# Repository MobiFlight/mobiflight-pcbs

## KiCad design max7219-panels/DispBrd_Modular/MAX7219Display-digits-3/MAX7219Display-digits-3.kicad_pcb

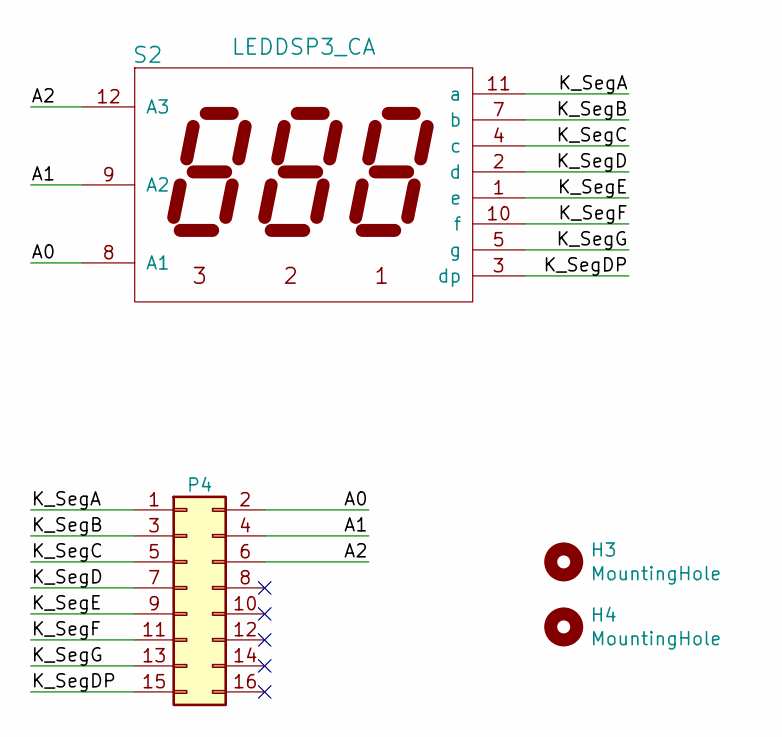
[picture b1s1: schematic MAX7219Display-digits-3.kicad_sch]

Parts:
H3, H4: MountingHole; Hole3mm
P4: Conn_02x08_Odd_Even; IDC-Header_2x08_P2.54mm_Vertical
S2: LEDDSP3_CA; Disp7s3x_036

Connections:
/A0: P4.2, S2.8 (A1)
/A1: P4.4, S2.9 (A2)
/A2: P4.6, S2.12 (A3)
/K_SegA: P4.1, S2.11 (a)
/K_SegB: P4.3, S2.7 (b)
/K_SegC: P4.5, S2.4 (c)
/K_SegD: P4.7, S2.2 (d)
/K_SegDP: P4.15, S2.3 (dp)
/K_SegE: P4.9, S2.1 (e)
/K_SegF: P4.11, S2.10 (f)
/K_SegG: P4.13, S2.5 (g)

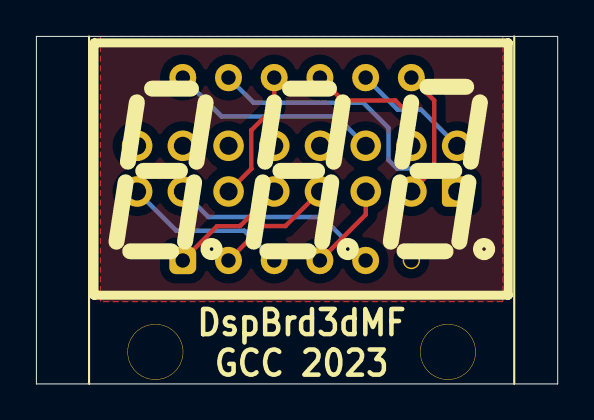
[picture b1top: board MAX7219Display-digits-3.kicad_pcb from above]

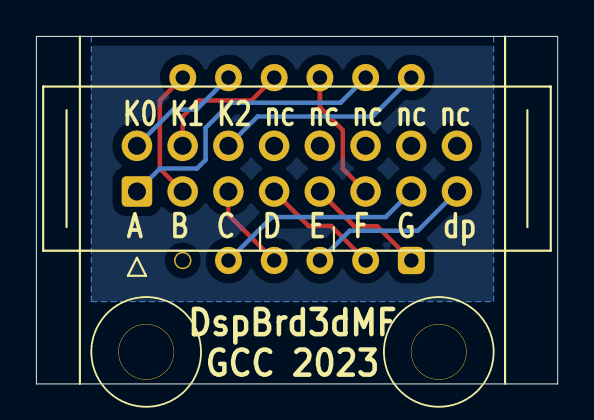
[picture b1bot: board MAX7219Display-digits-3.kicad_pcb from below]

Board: 2 copper layers, 29.0 x 19.3 mm, 4 parts (3 on the bottom side), 11 nets.

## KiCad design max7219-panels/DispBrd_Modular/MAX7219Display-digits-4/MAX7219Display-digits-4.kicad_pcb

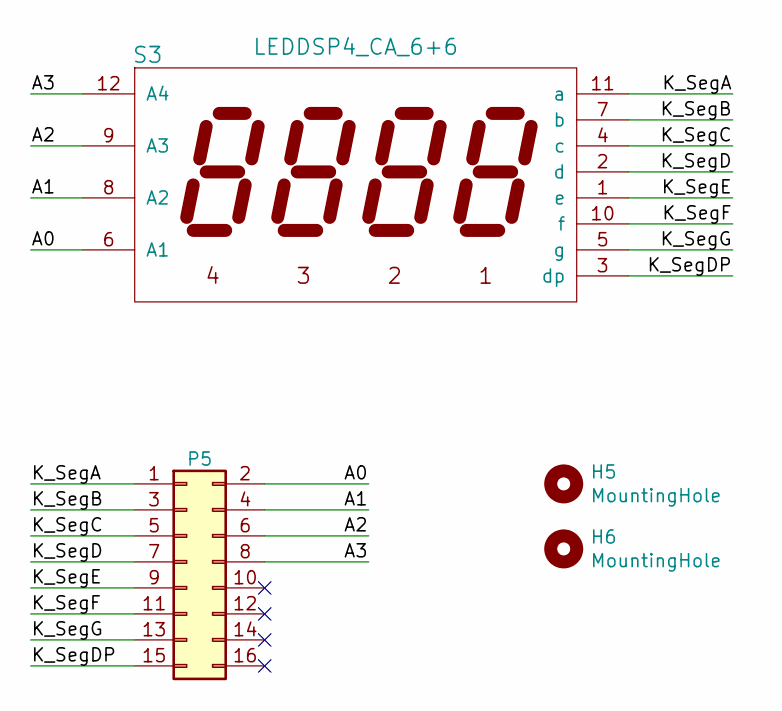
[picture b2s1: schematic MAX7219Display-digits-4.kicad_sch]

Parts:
H5, H6: MountingHole; Hole3mm
P5: Conn_02x08_Odd_Even; IDC-Header_2x08_P2.54mm_Vertical
S3: LEDDSP4_CA_6+6; Disp7s4x_036_6+6

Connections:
/A0: P5.2, S3.6 (A1)
/A1: P5.4, S3.8 (A2)
/A2: P5.6, S3.9 (A3)
/A3: P5.8, S3.12 (A4)
/K_SegA: P5.1, S3.11 (a)
/K_SegB: P5.3, S3.7 (b)
/K_SegC: P5.5, S3.4 (c)
/K_SegD: P5.7, S3.2 (d)
/K_SegDP: P5.15, S3.3 (dp)
/K_SegE: P5.9, S3.1 (e)
/K_SegF: P5.11, S3.10 (f)
/K_SegG: P5.13, S3.5 (g)

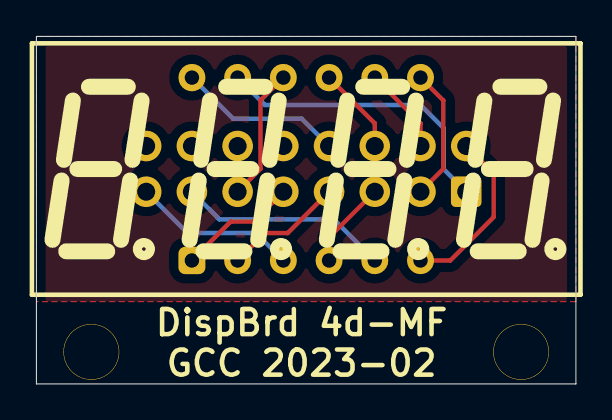
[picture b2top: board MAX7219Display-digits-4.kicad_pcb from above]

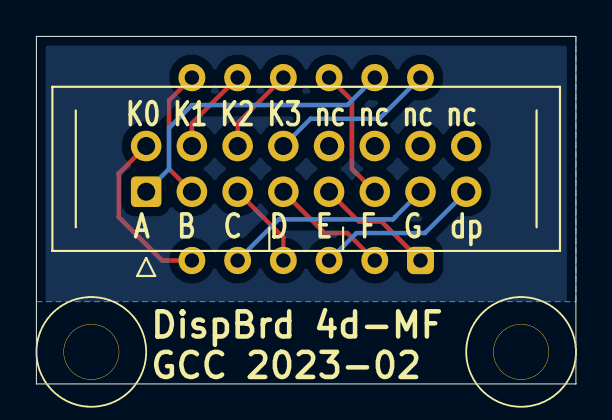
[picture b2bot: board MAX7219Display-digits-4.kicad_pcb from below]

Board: 2 copper layers, 30.0 x 19.3 mm, 4 parts (3 on the bottom side), 12 nets.

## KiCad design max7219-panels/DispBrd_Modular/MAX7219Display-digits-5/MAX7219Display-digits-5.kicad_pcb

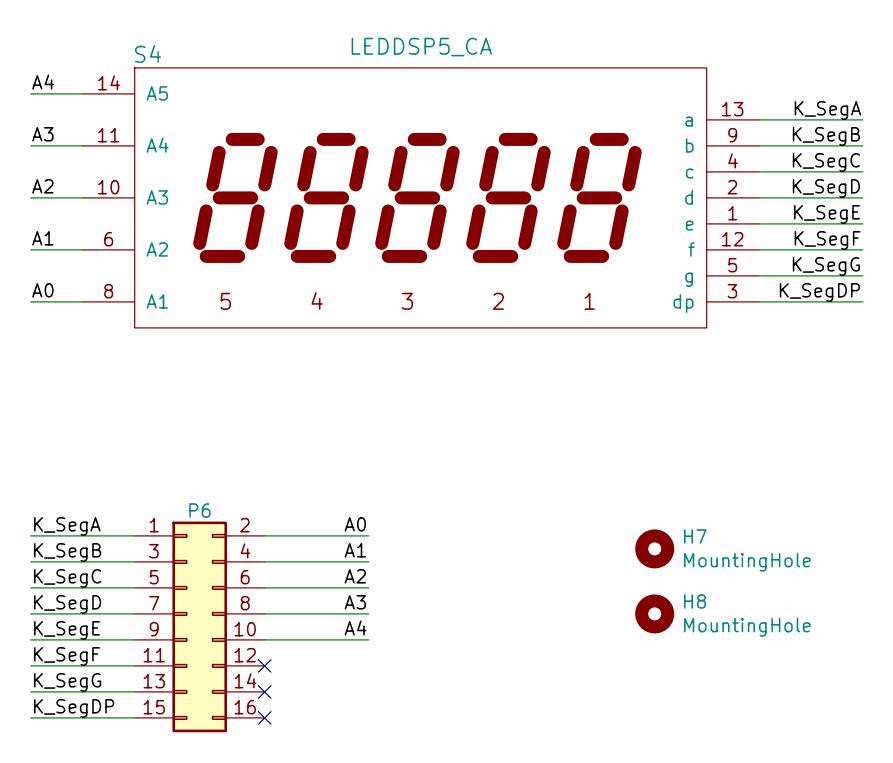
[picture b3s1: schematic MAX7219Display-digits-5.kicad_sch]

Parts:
H7, H8: MountingHole; Hole3mm
P6: Conn_02x08_Odd_Even; IDC-Header_2x08_P2.54mm_Vertical
S4: LEDDSP5_CA; Disp7s5x_036

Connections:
/A0: P6.2, S4.8 (A1)
/A1: P6.4, S4.6 (A2)
/A2: P6.6, S4.10 (A3)
/A3: P6.8, S4.11 (A4)
/A4: P6.10, S4.14 (A5)
/K_SegA: P6.1, S4.13 (a)
/K_SegB: P6.3, S4.9 (b)
/K_SegC: P6.5, S4.4 (c)
/K_SegD: P6.7, S4.2 (d)
/K_SegDP: P6.15, S4.3 (dp)
/K_SegE: P6.9, S4.1 (e)
/K_SegF: P6.11, S4.12 (f)
/K_SegG: P6.13, S4.5 (g)

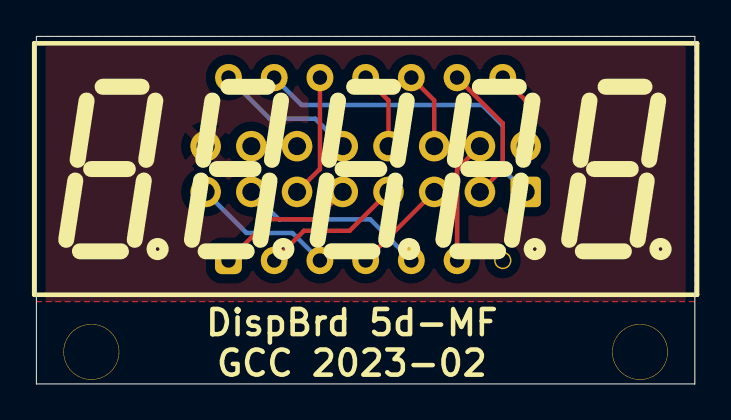
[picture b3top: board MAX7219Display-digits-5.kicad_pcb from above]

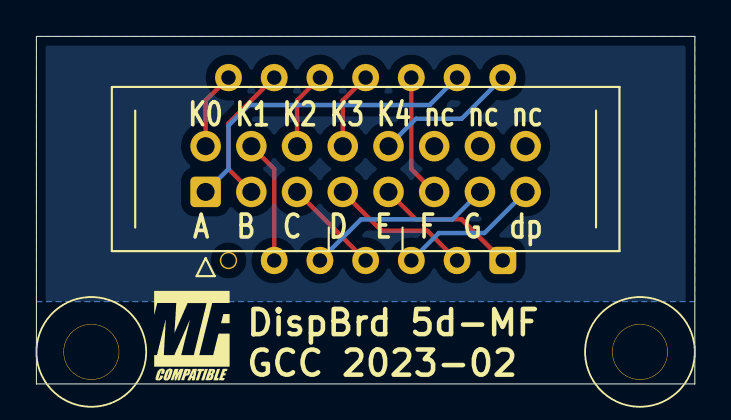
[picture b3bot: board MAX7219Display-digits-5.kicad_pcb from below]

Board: 2 copper layers, 36.6 x 19.3 mm, 4 parts (3 on the bottom side), 13 nets.

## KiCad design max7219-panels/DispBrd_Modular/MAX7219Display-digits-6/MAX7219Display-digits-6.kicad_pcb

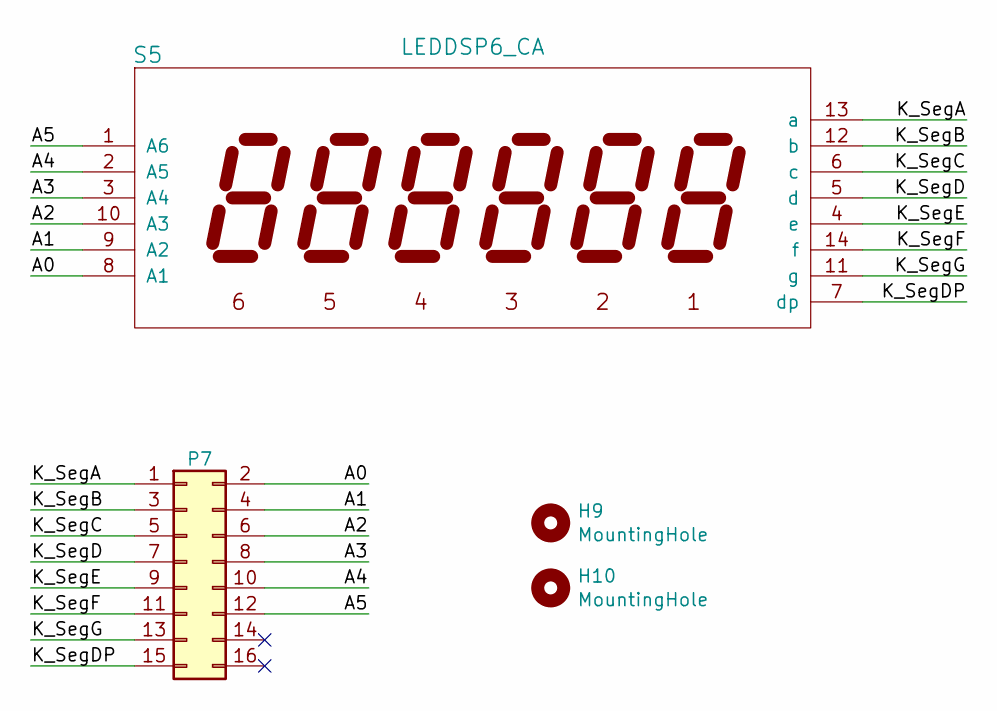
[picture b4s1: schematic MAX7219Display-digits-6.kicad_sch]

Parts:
H9, H10: MountingHole; Hole3mm
P7: Conn_02x08_Odd_Even; IDC-Header_2x08_P2.54mm_Vertical
S5: LEDDSP6_CA; Disp7s6x_036

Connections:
/A0: P7.2, S5.8 (A1)
/A1: P7.4, S5.9 (A2)
/A2: P7.6, S5.10 (A3)
/A3: P7.8, S5.3 (A4)
/A4: P7.10, S5.2 (A5)
/A5: P7.12, S5.1 (A6)
/K_SegA: P7.1, S5.13 (a)
/K_SegB: P7.3, S5.12 (b)
/K_SegC: P7.5, S5.6 (c)
/K_SegD: P7.7, S5.5 (d)
/K_SegDP: P7.15, S5.7 (dp)
/K_SegE: P7.9, S5.4 (e)
/K_SegF: P7.11, S5.14 (f)
/K_SegG: P7.13, S5.11 (g)

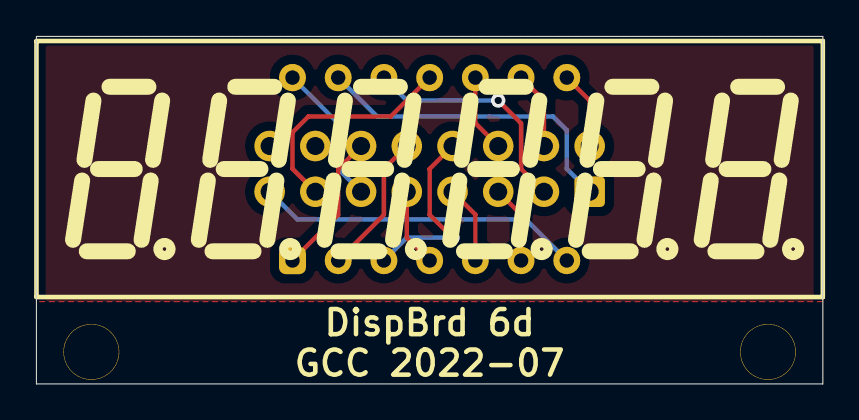
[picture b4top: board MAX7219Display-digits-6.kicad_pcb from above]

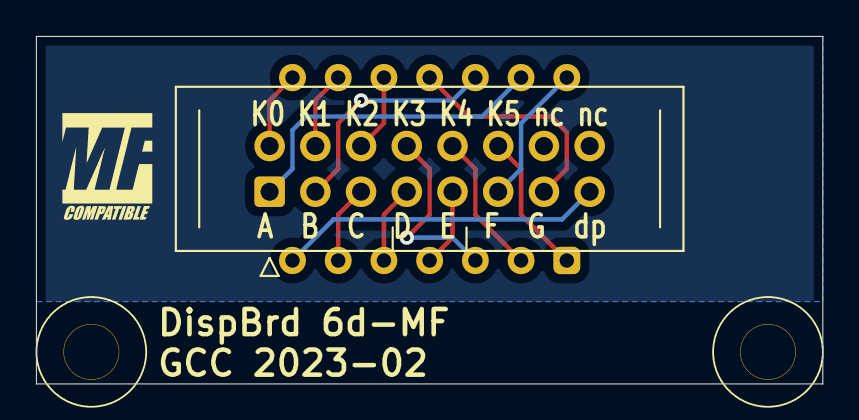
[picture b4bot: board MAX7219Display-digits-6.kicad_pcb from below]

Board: 2 copper layers, 43.7 x 19.3 mm, 4 parts (3 on the bottom side), 14 nets.

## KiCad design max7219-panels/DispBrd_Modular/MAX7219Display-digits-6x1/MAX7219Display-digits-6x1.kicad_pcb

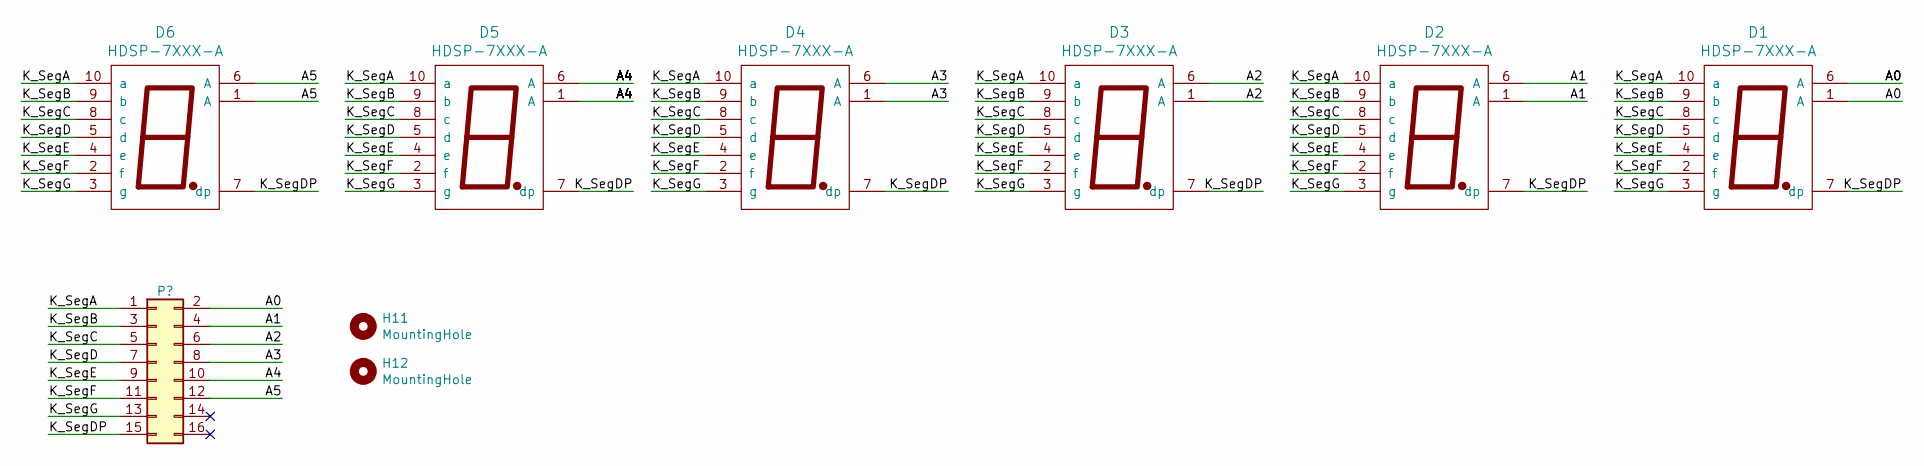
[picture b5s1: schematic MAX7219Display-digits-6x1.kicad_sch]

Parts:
D1, D2, D3, D4, D5, D6: HDSP-7XXX-A; Disp7_036
H11, H12: MountingHole; Hole3mm

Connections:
/A0: D1.1 (A), D1.6 (A); also elsewhere on the board
/A1: D2.1 (A), D2.6 (A); also elsewhere on the board
/A2: D3.1 (A), D3.6 (A); also elsewhere on the board
/A3: D4.1 (A), D4.6 (A); also elsewhere on the board
/A4: D5.1 (A), D5.6 (A); also elsewhere on the board
/A5: D6.1 (A), D6.6 (A); also elsewhere on the board
/K_SegA: D1.10 (a), D2.10 (a), D3.10 (a), D4.10 (a), D5.10 (a), D6.10 (a); also elsewhere on the board
/K_SegB: D1.9 (b), D2.9 (b), D3.9 (b), D4.9 (b), D5.9 (b), D6.9 (b); also elsewhere on the board
/K_SegC: D1.8 (c), D2.8 (c), D3.8 (c), D4.8 (c), D5.8 (c), D6.8 (c); also elsewhere on the board
/K_SegD: D1.5 (d), D2.5 (d), D3.5 (d), D4.5 (d), D5.5 (d), D6.5 (d); also elsewhere on the board
/K_SegDP: D1.7 (dp), D2.7 (dp), D3.7 (dp), D4.7 (dp), D5.7 (dp), D6.7 (dp); also elsewhere on the board
/K_SegE: D1.4 (e), D2.4 (e), D3.4 (e), D4.4 (e), D5.4 (e), D6.4 (e); also elsewhere on the board
/K_SegF: D1.2 (f), D2.2 (f), D3.2 (f), D4.2 (f), D5.2 (f), D6.2 (f); also elsewhere on the board
/K_SegG: D1.3 (g), D2.3 (g), D3.3 (g), D4.3 (g), D5.3 (g), D6.3 (g); also elsewhere on the board

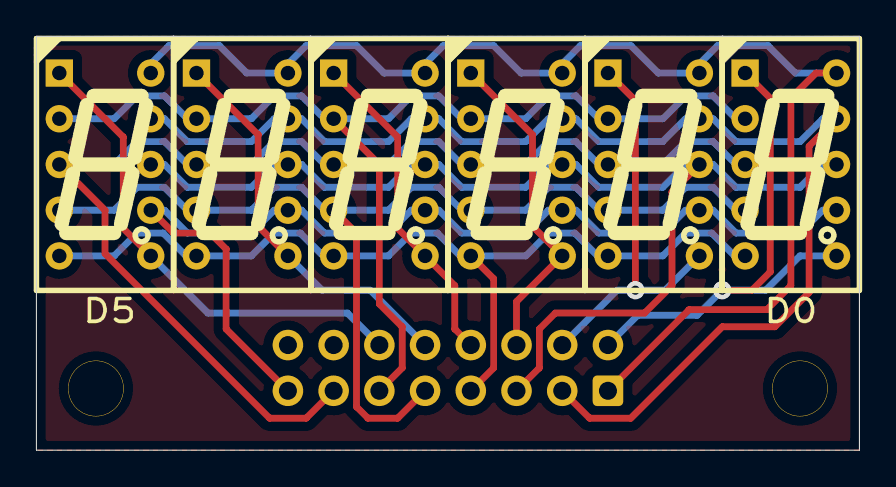
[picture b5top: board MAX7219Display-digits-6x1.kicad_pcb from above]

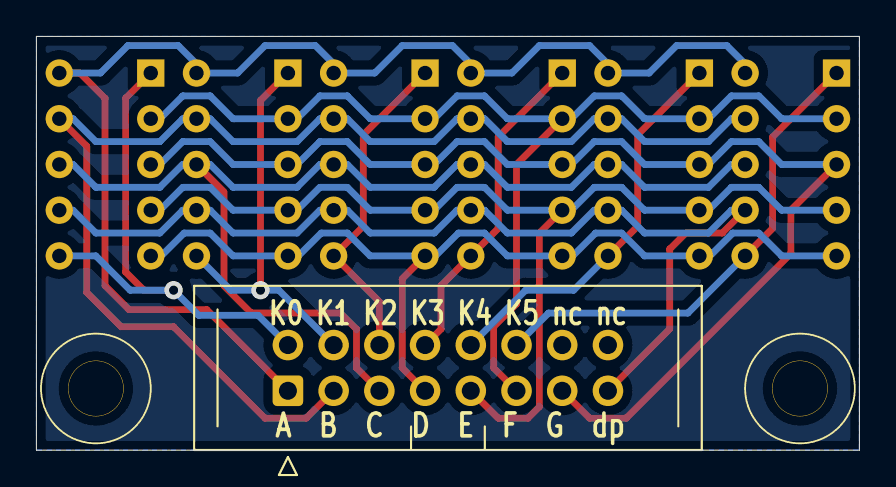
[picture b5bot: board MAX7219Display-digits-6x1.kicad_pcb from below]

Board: 2 copper layers, 45.7 x 23.0 mm, 9 parts (3 on the bottom side), 14 nets.

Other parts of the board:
P8: Conn_02x08_Odd_Even; IDC-Header_2x08_P2.54mm_Vertical

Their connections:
/A0: P8.2; also elsewhere on the board
/A1: P8.4; also elsewhere on the board
/A2: P8.6; also elsewhere on the board
/A3: P8.8; also elsewhere on the board
/A4: P8.10; also elsewhere on the board
/A5: P8.12; also elsewhere on the board
/K_SegA: P8.1; also elsewhere on the board
/K_SegB: P8.3; also elsewhere on the board
/K_SegC: P8.5; also elsewhere on the board
/K_SegD: P8.7; also elsewhere on the board
/K_SegDP: P8.15; also elsewhere on the board
/K_SegE: P8.9; also elsewhere on the board
/K_SegF: P8.11; also elsewhere on the board
/K_SegG: P8.13; also elsewhere on the board

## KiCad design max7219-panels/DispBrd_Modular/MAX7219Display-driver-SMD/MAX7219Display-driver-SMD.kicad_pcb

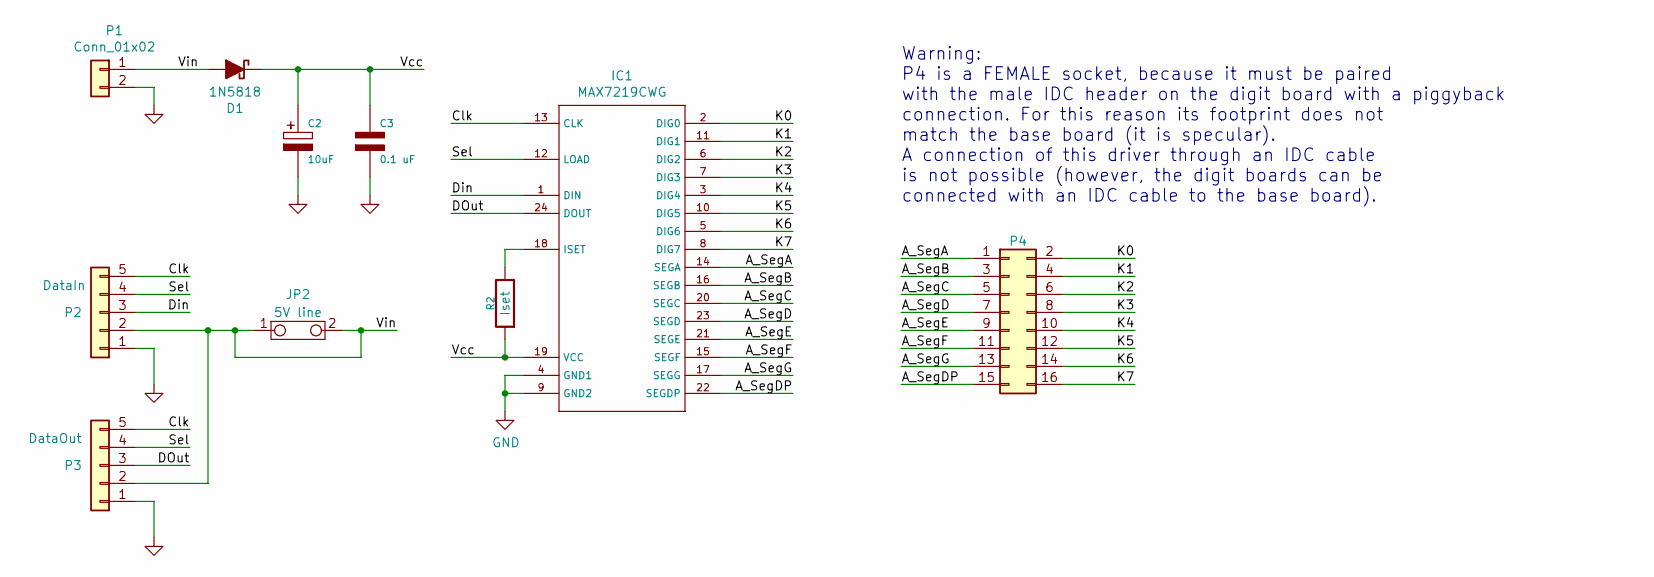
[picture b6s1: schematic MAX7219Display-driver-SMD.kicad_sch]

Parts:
C2: 10uF; CP_Radial_D5.0mm_P2.50mm
C3: 0.1 uF; C_1206_3216Metric_Pad1.42x1.75mm_HandSolder
D1: 1N5818; D_SMA_Handsoldering
IC1: MAX7219CWG; SOIC-24W_7.5x15.4mm_P1.27mm
JP2: 5V line; SolderJumper-2_P1.3mm_Bridged_Pad1.0x1.5mm
P1: Conn_01x02; PinHeader_1x02_P2.54mm_Vertical
P2: DataIn; JST_XH_B5B-XH-A_1x05_P2.50mm_Vertical
P3: DataOut; JST_XH_B5B-XH-A_1x05_P2.50mm_Vertical
P4: Conn_02x08_Odd_Even; PinSocket_2x08_P2.54mm_Vertical_SMD
R2: Iset; R_Axial_DIN0207_L6.3mm_D2.5mm_P10.16mm_Horizontal

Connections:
/A_SegA: IC1.14 (SEGA), P4.1
/A_SegB: IC1.16 (SEGB), P4.3
/A_SegC: IC1.20 (SEGC), P4.5
/A_SegD: IC1.23 (SEGD), P4.7
/A_SegDP: IC1.22 (SEGDP), P4.15
/A_SegE: IC1.21 (SEGE), P4.9
/A_SegF: IC1.15 (SEGF), P4.11
/A_SegG: IC1.17 (SEGG), P4.13
/Clk: IC1.13 (CLK), P2.5, P3.5
/DOut: IC1.24 (DOUT), P3.3
/Din: IC1.1 (DIN), P2.3
/K0: IC1.2 (DIG0), P4.2
/K1: IC1.11 (DIG1), P4.4
/K2: IC1.6 (DIG2), P4.6
/K3: IC1.7 (DIG3), P4.8
/K4: IC1.3 (DIG4), P4.10
/K5: IC1.10 (DIG5), P4.12
/K6: IC1.5 (DIG6), P4.14
/K7: IC1.8 (DIG7), P4.16
/Sel: IC1.12 (LOAD), P2.4, P3.4
/Vcc: C2.1, C3.1, D1.1 (K), IC1.19 (VCC), R2.1
/Vin: D1.2 (A), JP2.1, JP2.2, P1.1, P2.2, P3.2
GND: C2.2, C3.2, IC1.4 (GND1), IC1.9 (GND2), P1.2, P2.1, P3.1
unnamed: IC1.18 (ISET), R2.2

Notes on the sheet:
Warning: P4 is a FEMALE socket, because it must be paired with the male IDC header on the digit board with a piggyback connection. For this reason its footprint does not match the base board (it is specular). A connection of this driver through an IDC cable is not possible (however, the digit board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

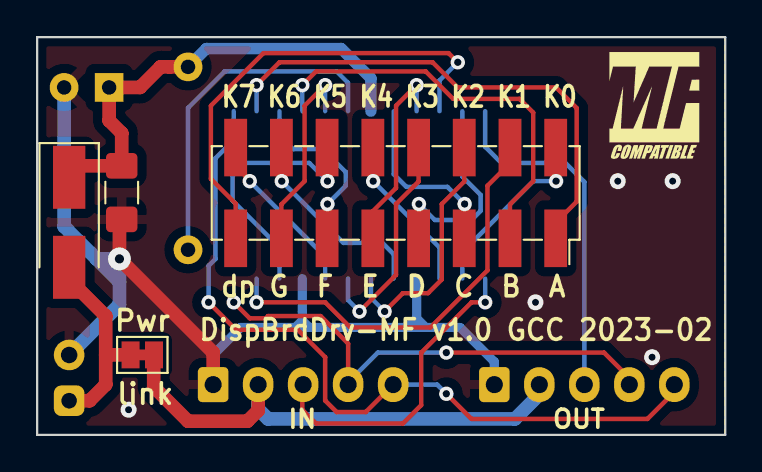
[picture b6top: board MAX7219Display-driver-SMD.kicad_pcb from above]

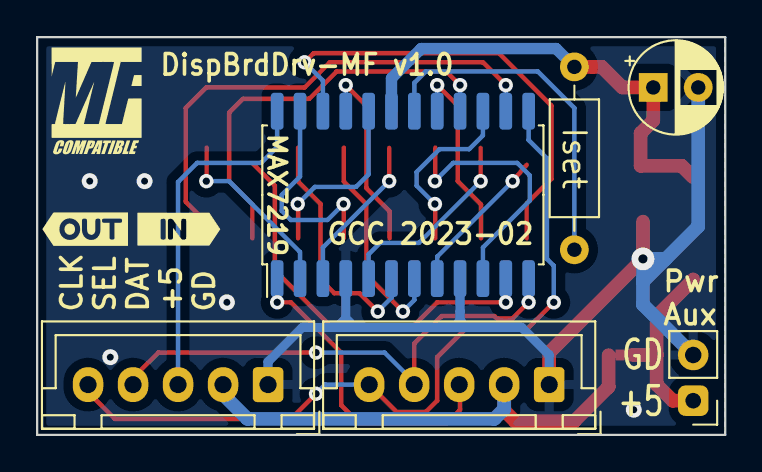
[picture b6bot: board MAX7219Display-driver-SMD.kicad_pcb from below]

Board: 2 copper layers, 38.2 x 22.1 mm, 12 parts (8 on the bottom side), 24 nets.

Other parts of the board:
kibuzzard-6405E11D: G***; kibuzzard-6405E11D
kibuzzard-6405E116: G***; kibuzzard-6405E116
